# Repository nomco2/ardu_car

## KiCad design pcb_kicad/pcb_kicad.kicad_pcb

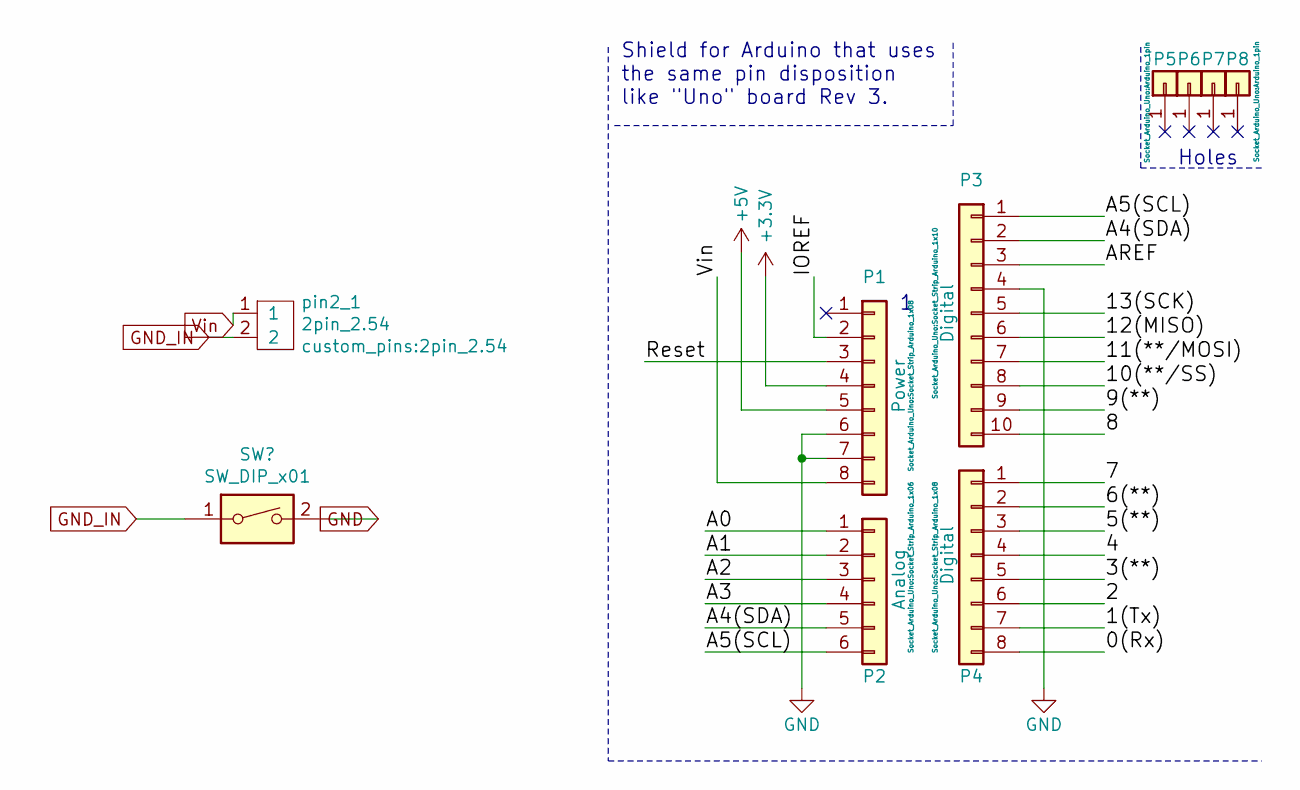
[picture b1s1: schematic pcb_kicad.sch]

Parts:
P1: Power; Socket_Strip_Arduino_1x08
P2: Analog; Socket_Strip_Arduino_1x06
P3: Digital; Socket_Strip_Arduino_1x10
P4: Digital; Socket_Strip_Arduino_1x08
P5, P6, P7, P8: CONN_01X01; Arduino_1pin
pin2_1: 2pin_2.54

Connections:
+3V3: P1.4
+5V: P1.5
/0(Rx): P4.8
/1(Tx): P4.7
/2: P4.6
/3(**): P4.5
/4: P4.4
/5(**): P4.3
/6(**): P4.2
/7: P4.1
/8: P3.10
/9(**): P3.9
/10(**/SS): P3.8
/11(**/MOSI): P3.7
/12(MISO): P3.6
/13(SCK): P3.5
/A0: P2.1
/A1: P2.2
/A2: P2.3
/A3: P2.4
/A4(SDA): P2.5, P3.2
/A5(SCL): P2.6, P3.1
/AREF: P3.3
/IOREF: P1.2
/Reset: P1.3
Vin: P1.8, pin2_1.1

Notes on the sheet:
Holes
Shield for Arduino that uses the same pin disposition like "Uno" board Rev 3.

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
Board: 2 copper layers, 9 parts (0 on the bottom side), 4 nets, no tracks yet.

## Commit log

2017-10-23 first_saved
2017-10-23 movable_add
2017-10-23 button1_image_add
2017-10-25 move_text_invisible
2017-10-25 data_saving_operation_dev_not_complite
2017-10-29 get_address_function
2017-11-11 auto_creating_operation_buttons
2017-11-14 buttons_auto_creating_add
2022-02-26 ki cad
